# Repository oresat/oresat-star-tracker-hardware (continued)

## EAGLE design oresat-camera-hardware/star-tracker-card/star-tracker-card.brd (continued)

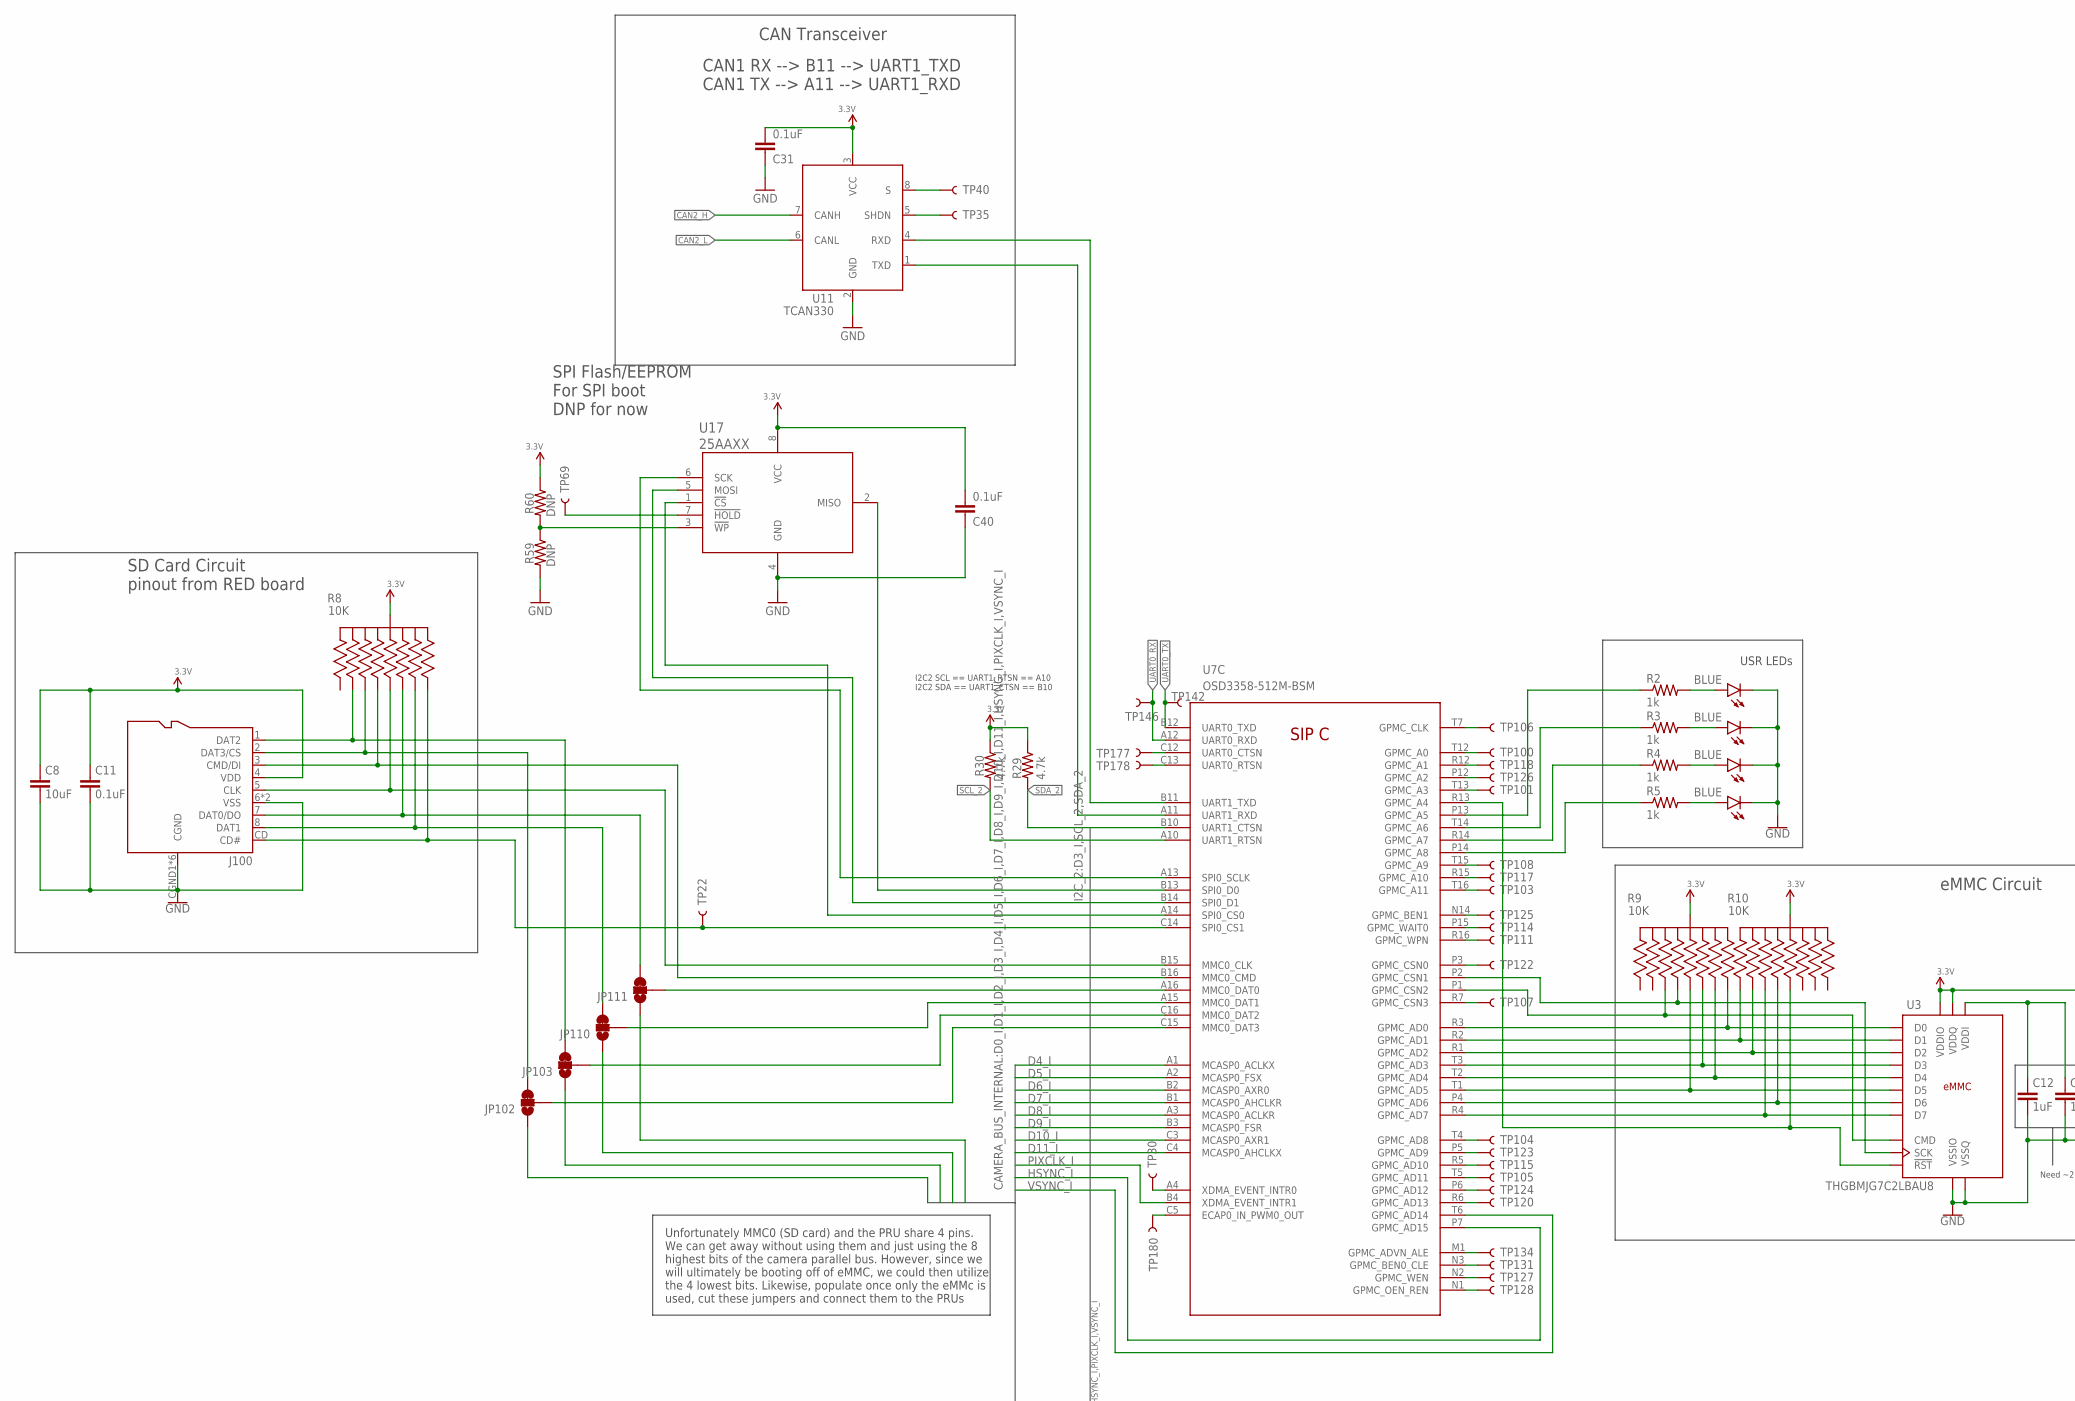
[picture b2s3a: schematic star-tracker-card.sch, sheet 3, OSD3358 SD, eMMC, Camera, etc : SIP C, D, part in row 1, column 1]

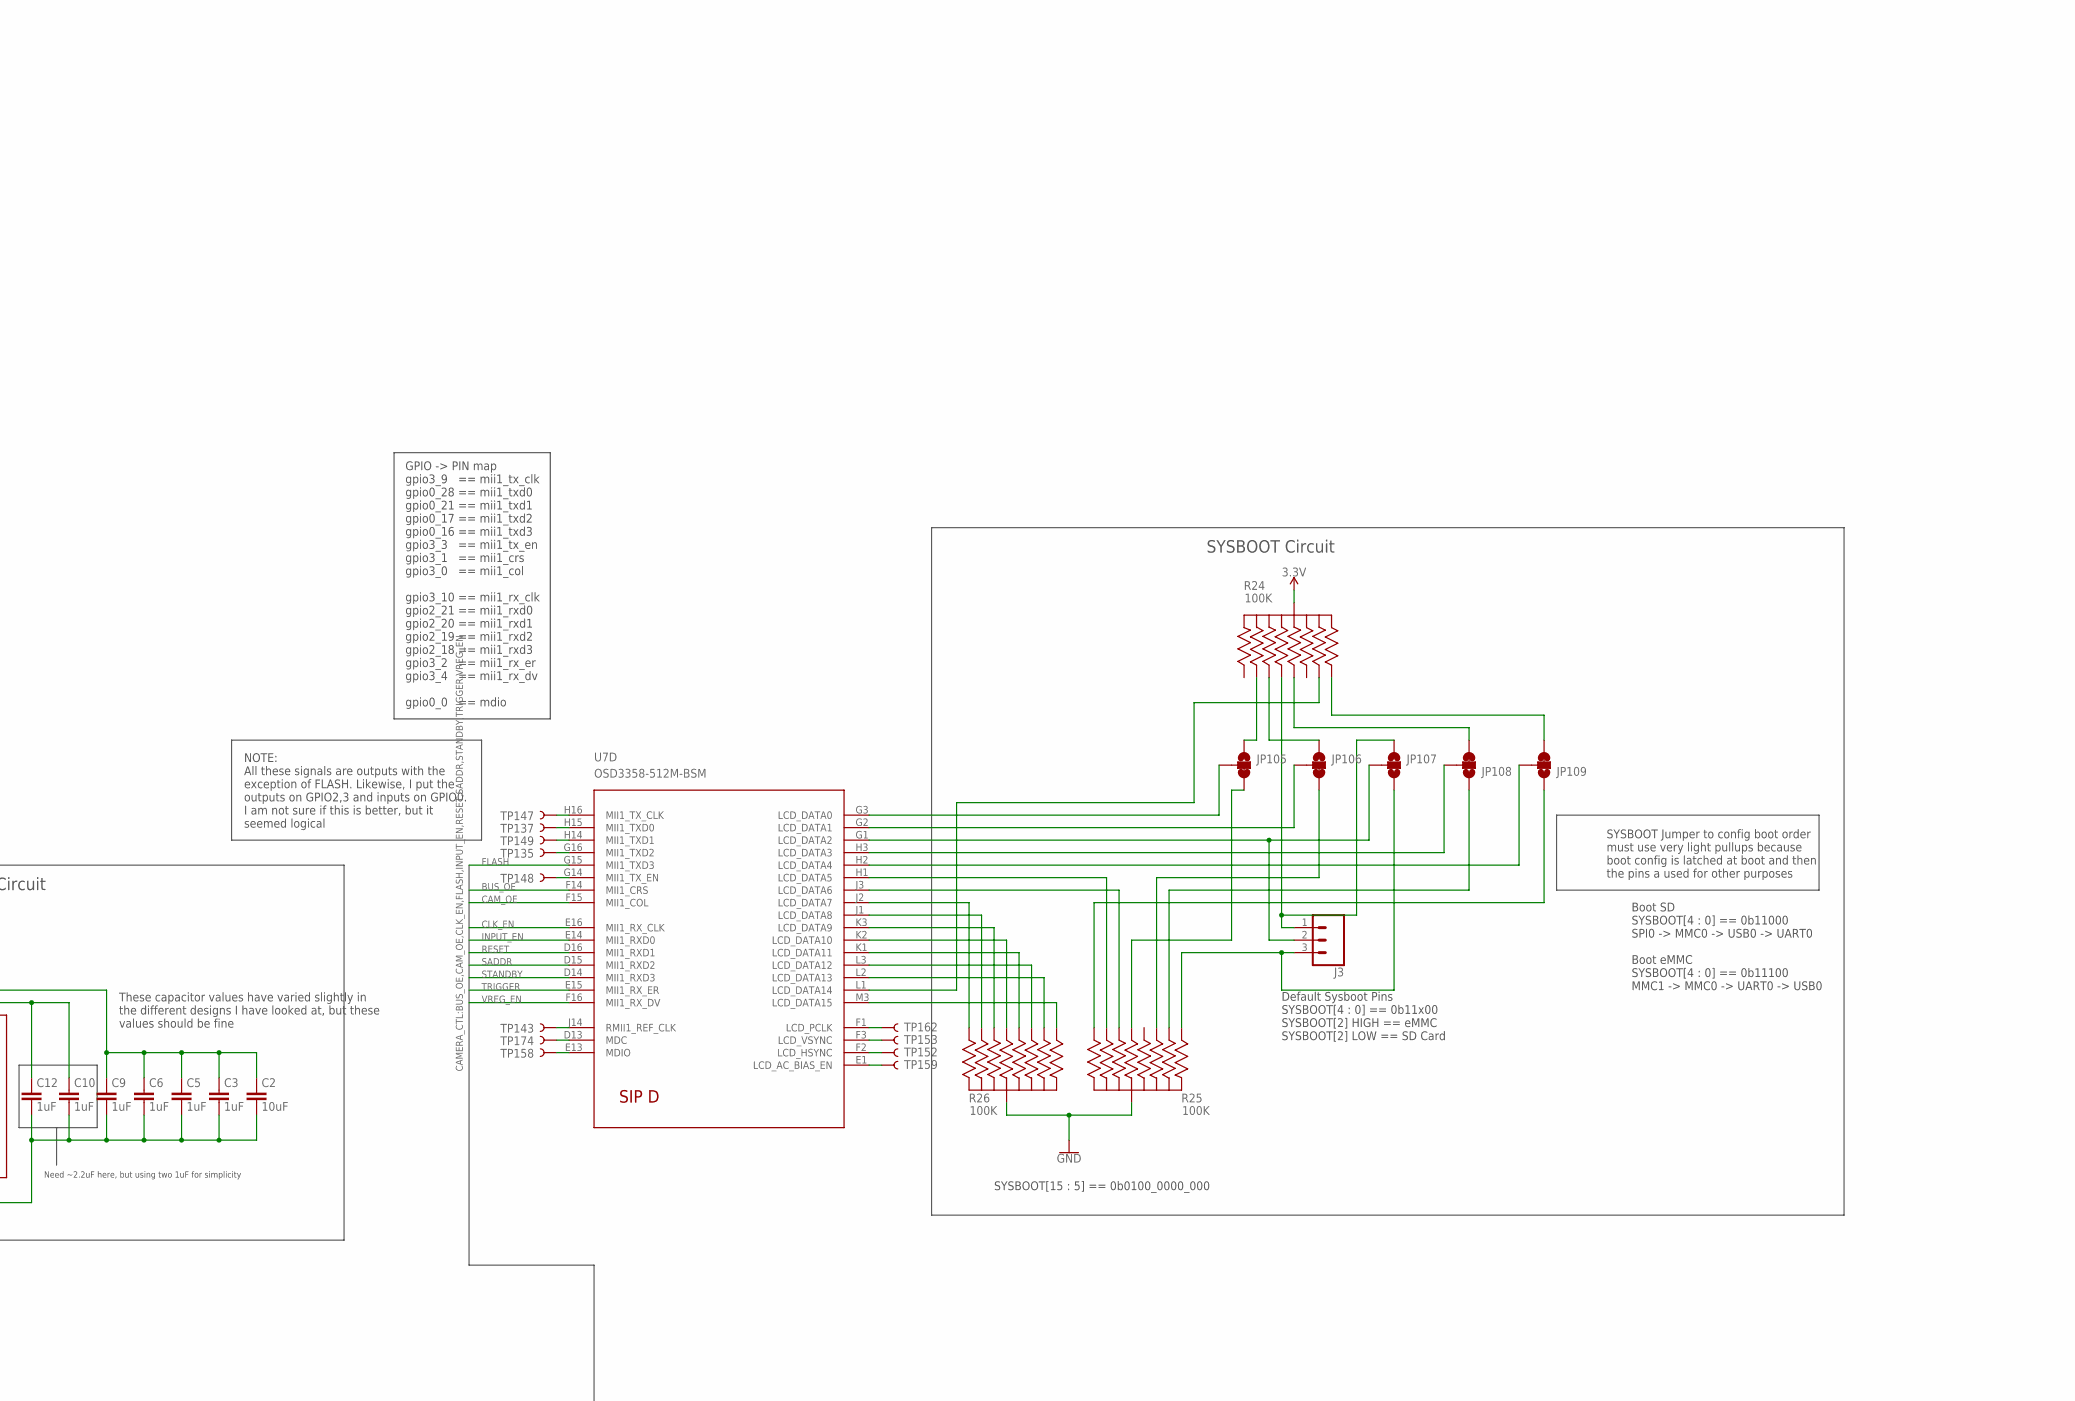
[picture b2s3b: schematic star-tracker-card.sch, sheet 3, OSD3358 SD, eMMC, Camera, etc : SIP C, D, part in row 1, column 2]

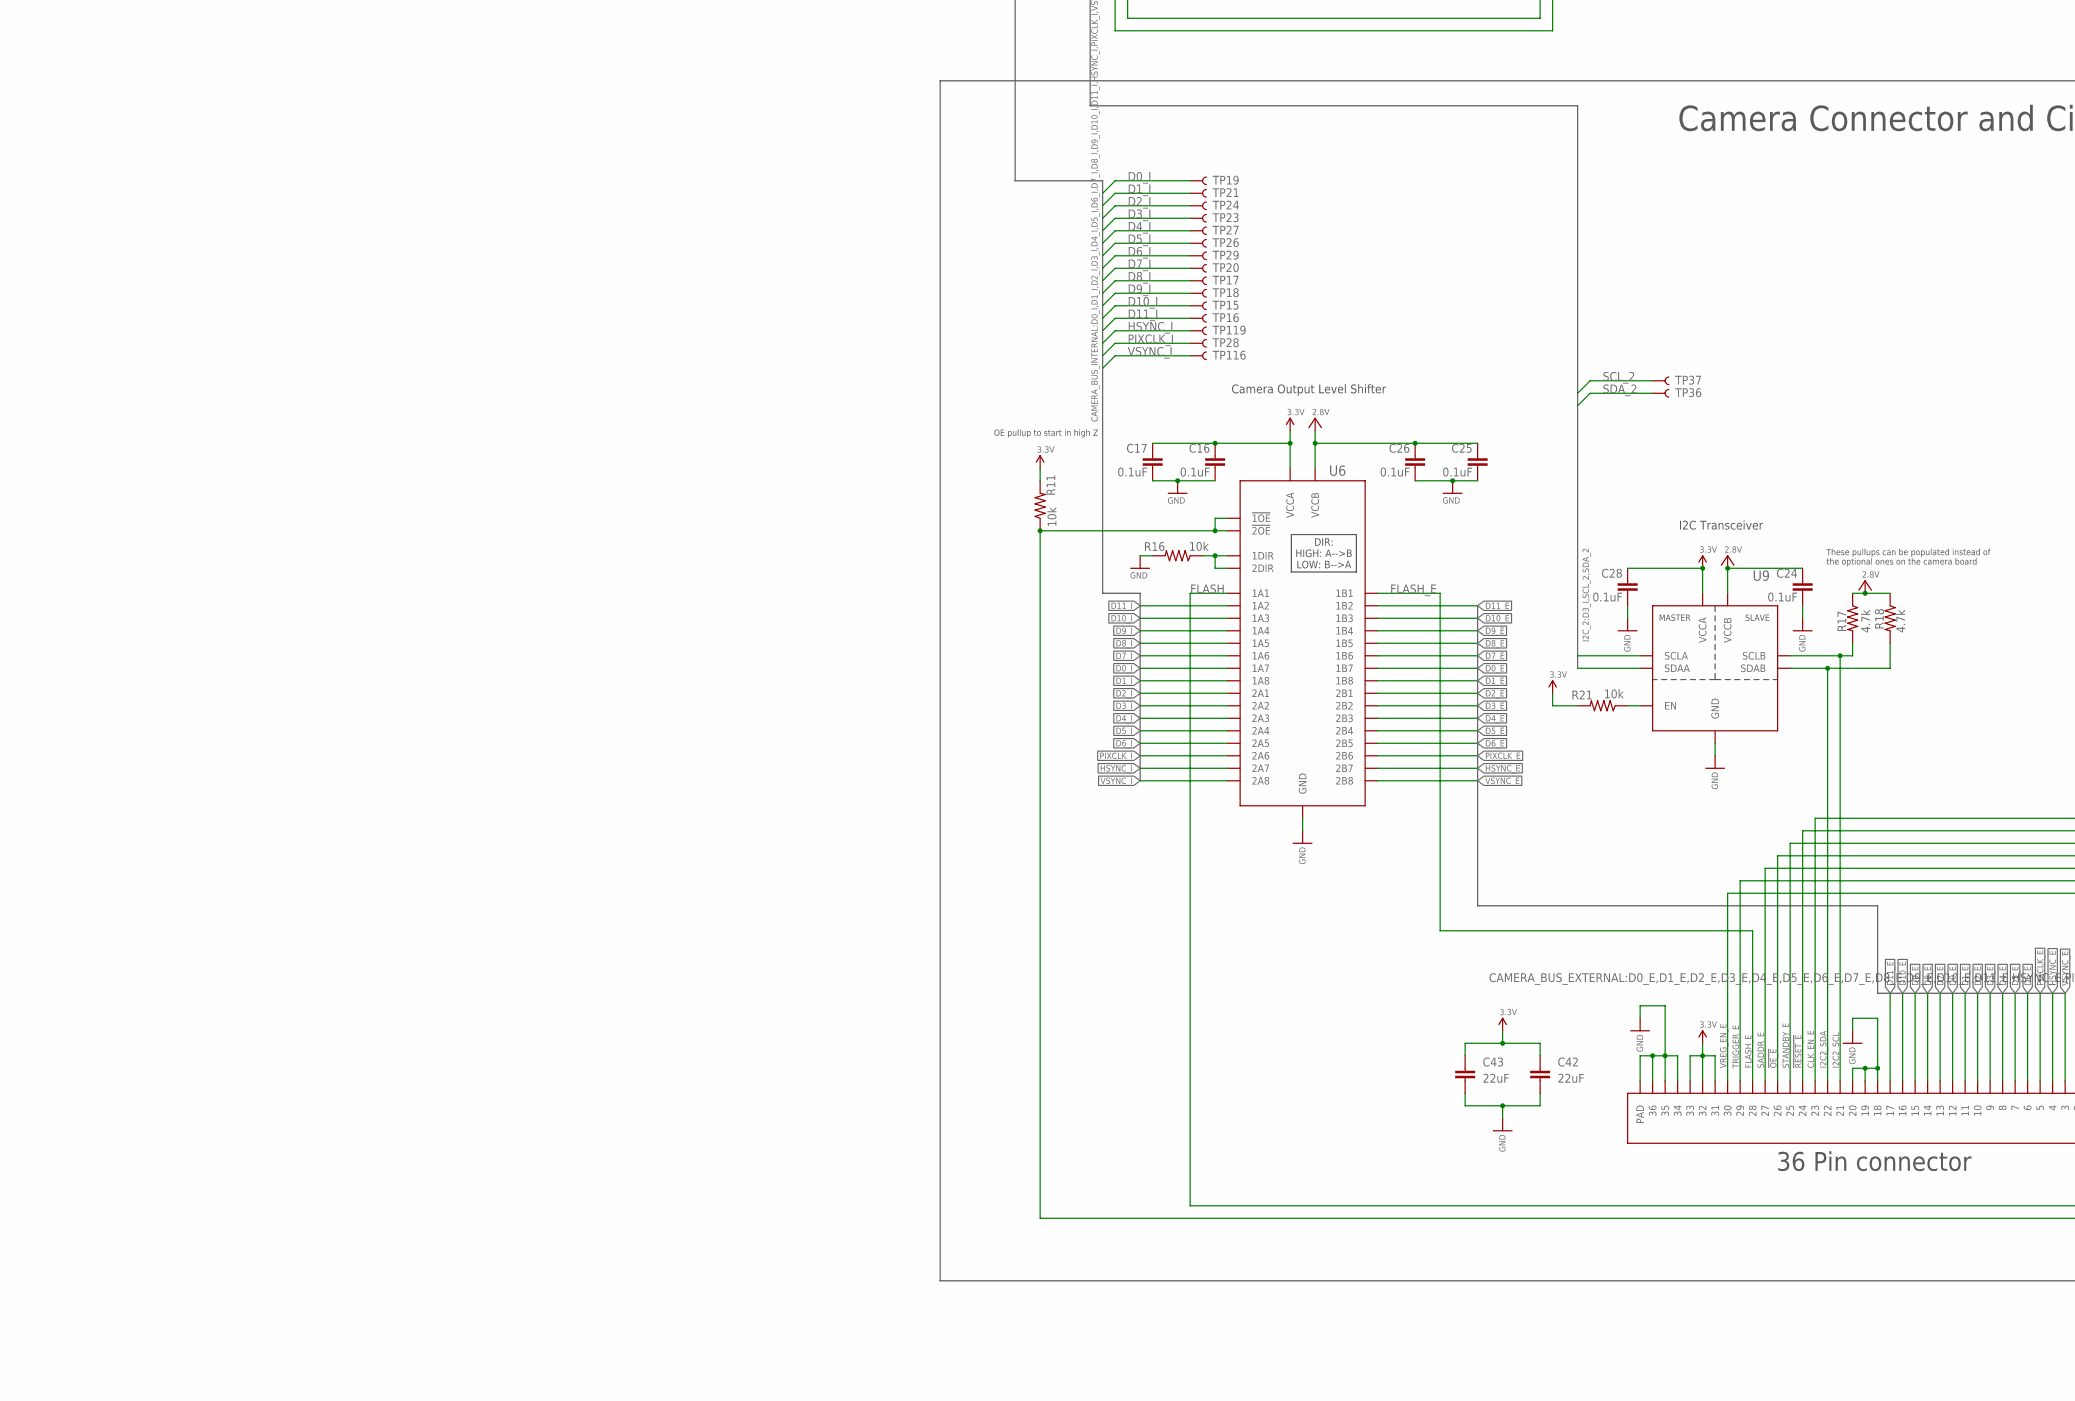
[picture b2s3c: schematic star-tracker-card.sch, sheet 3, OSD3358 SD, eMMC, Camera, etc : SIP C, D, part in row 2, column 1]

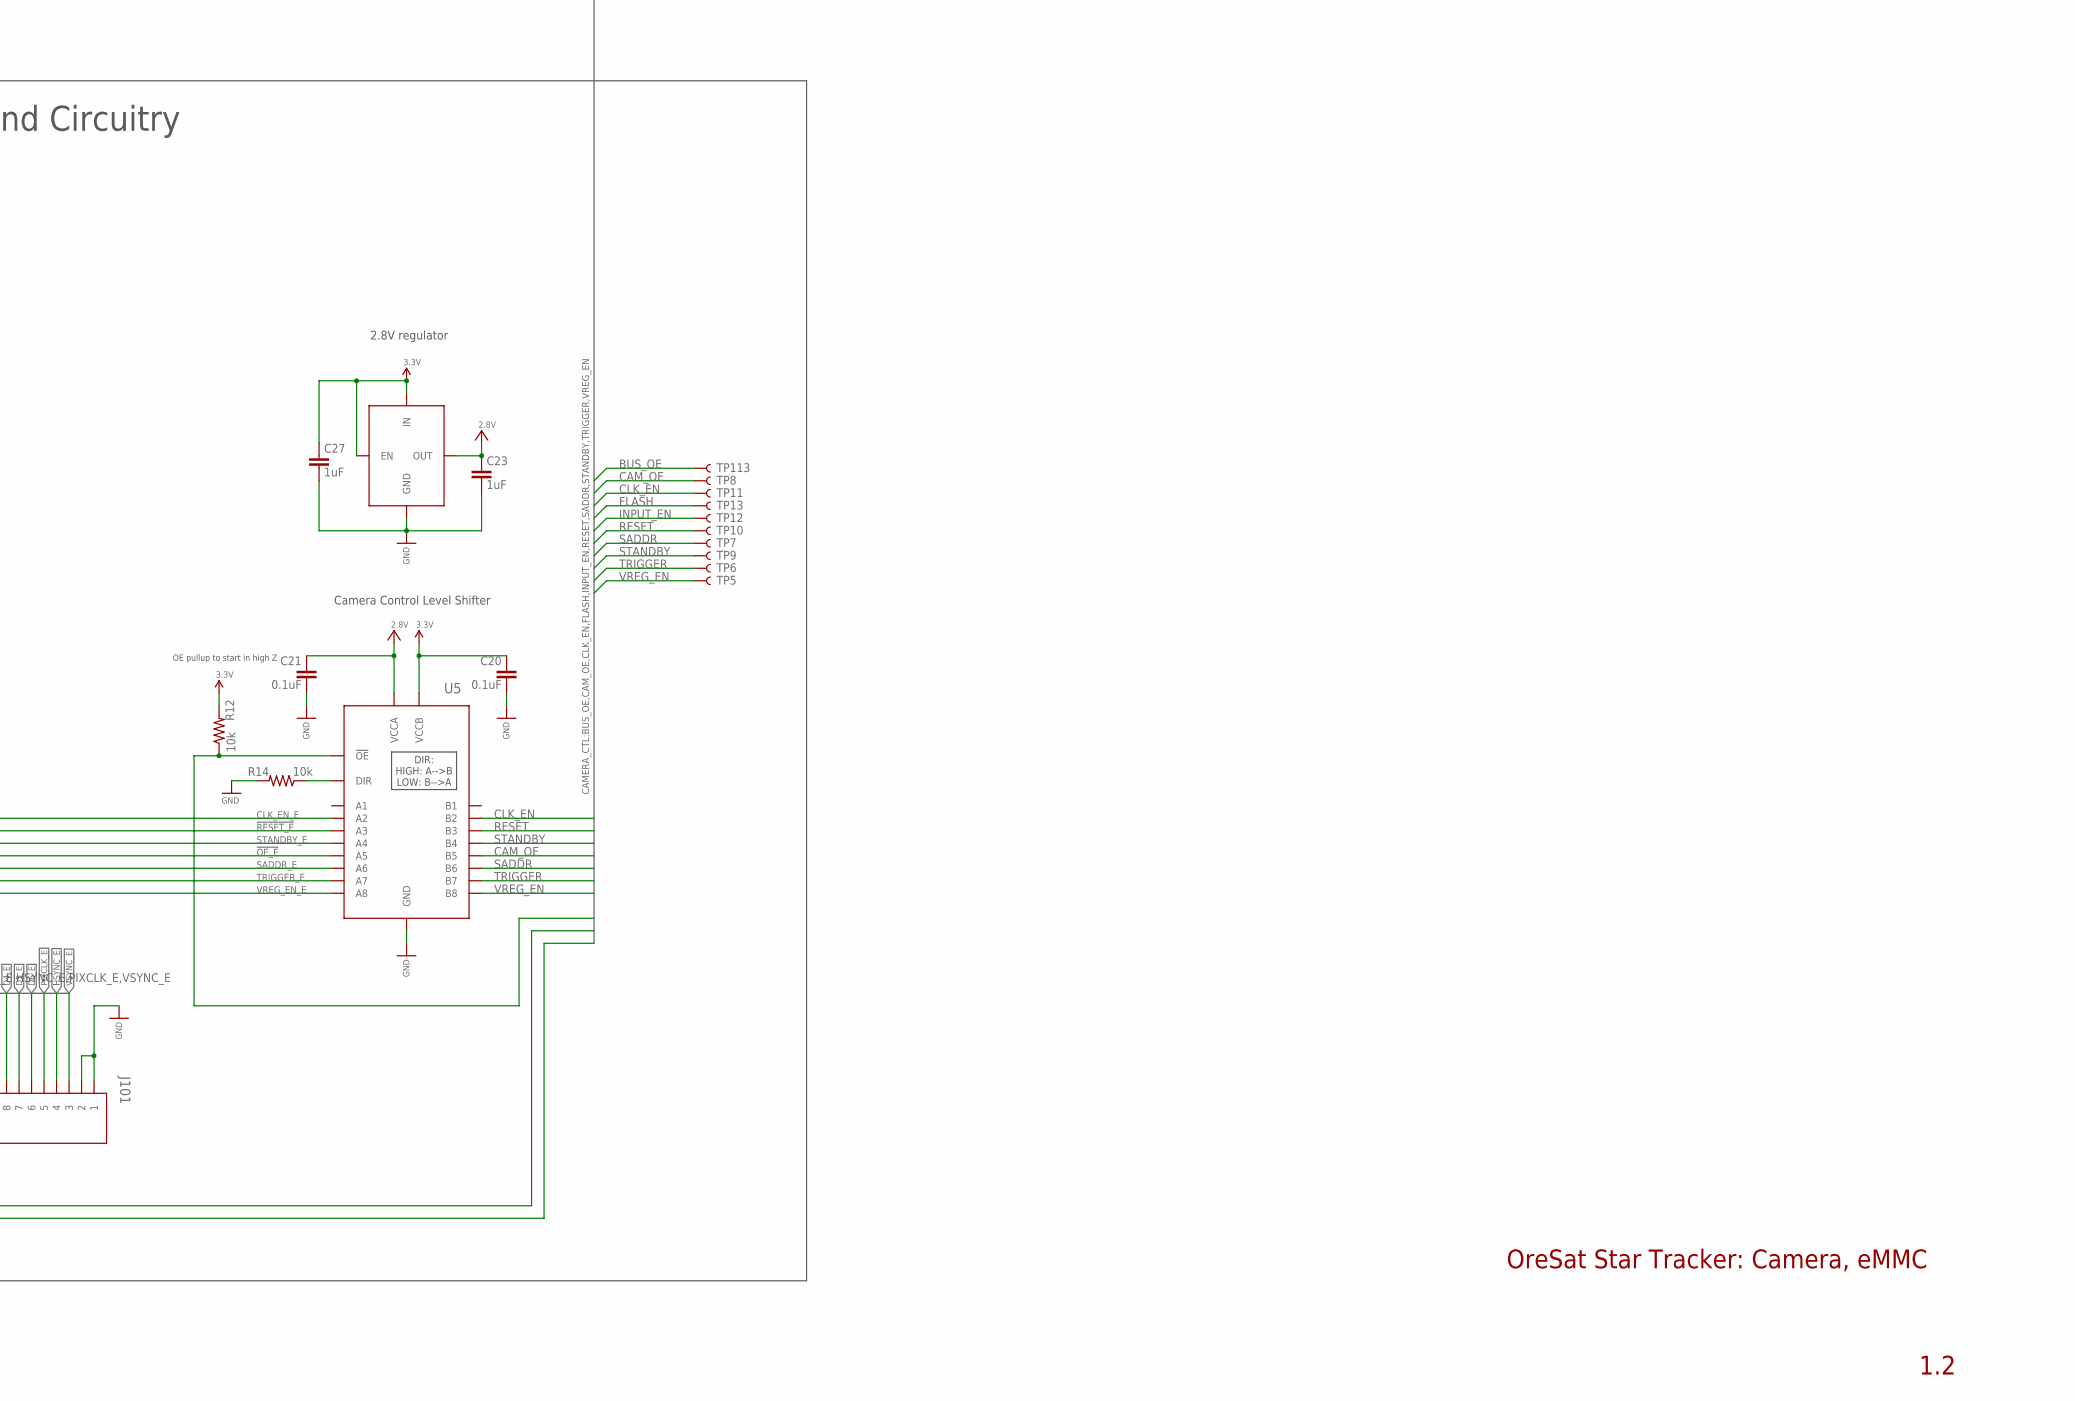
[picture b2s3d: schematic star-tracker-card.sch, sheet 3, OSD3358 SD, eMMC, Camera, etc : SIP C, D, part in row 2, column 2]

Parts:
C2, C8: 10uF; .0805-B
C3, C5, C6, C9, C10, C12, C23, C27: 1uF; .0603-A
C11, C16, C17, C20, C21, C24, C25, C26, C28, C31, C40: 0.1uF; .0603-A
C42, C43: 22uF; C1210
D2, D3, D4, D5: BLUE; LED-0603
J3: CONN_03LONGPADS; 1X03_LONGPADS
J100: DM3BT-DSF-PEJS
J101: 3-1734592-64-1734592-0; TE_3-1734592-6
JP102, JP103, JP105, JP106, JP108, JP109, JP110, JP111: JUMPER-SMT_3_1-NC_TRACE_SILK; SMT-JUMPER_3_1-NC_TRACE_SILK
JP107: JUMPER-SMT_3_NO_SILK; SMT-JUMPER_3_NO_SILK
R2, R3, R4, R5: 1k; .0603-A
R8, R9, R10: 10K; ARRAY_EXBA-M; MPN EXB-A10P103J
R11, R12, R14, R16, R21: 10k; .0603-A
R17, R18, R29, R30: 4.7k; .0603-A
R24, R25, R26: 100K; ARRAY_EXBA-M; MPN EXB-A10P104J
R59, R60: DNP; .0603-A
TP5, TP6, TP7, TP8, TP9, TP10, TP11, TP12, TP13, TP15, TP16, TP17, TP18, TP19, TP20, TP21, TP22, TP23, TP24, TP26, TP27, TP28, TP29, TP30, TP35, TP36, TP37, TP40, TP69, TP100, TP101, TP103, TP104, TP105, TP106, TP107, TP108, TP111, TP113, TP114, TP115, TP116, TP117, TP118, TP119, TP120, TP122, TP123, TP124, TP125, TP126, TP127, TP128, TP131, TP134, TP135, TP137, TP142, TP143, TP146, TP147, TP148, TP149, TP152, TP153, TP158, TP159, TP162, TP174, TP177, TP178, TP180: TEST-POINT3X4; PAD.03X.04
U3: THGBMJG7C2LBAU8; BGA-153(11.5X13)(EMMC-BA); MPN THGBMJG7C2LBAU8
U5: SN74LVC8T245MPWREPPW24-M; PW24-M
U6: CLVCH16T245MDGGREP; DGG48-M
U7: OSD3358-512M-BSM; OSD335X-BGA-256
U8: TLV70028QDDCRQ1; SOT23-5
U9: TCA9509DGKRDGK8-M; DGK8-M
U11: TCAN330; SOT23-8_TI-DCN
U17: 25AAXX; SOIC8

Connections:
2.8V: C21.1, C23.1, C24.1, C25.1, C26.1, R17.1, R18.1, U5.1 (VCCA), U6.7 (VCCB), U6.18 (VCCB), U8.5 (OUT), U9.8 (VCCB)
3.3V: C2.1, C3.1, C5.1, C6.1, C8.1, C9.1, C11.1, C16.1, C17.1, C20.1, C27.1, C28.1, C31.2, C40.2, C42.1, C43.1, J100.4 (VDD), J101.31, J101.32, J101.33, R8.5 (55), R8.10 (55), R9.5 (55), R9.10 (55), R10.5 (55), R10.10 (55), R11.2, R12.2, R21.2, R24.5 (55), R24.10 (55), R29.1, R30.1, R60.1, U3.C6 (VDDQ), U3.E6 (VDDIO), U3.F5 (VDDIO), U3.J10 (VDDIO), U3.K9 (VDDIO), U3.M4 (VDDQ), U3.N4 (VDDQ), U3.P3 (VDDQ), U3.P5 (VDDQ), U5.23 (VCCB), U5.24 (VCCB), U6.31 (VCCA), U6.42 (VCCA), U8.1 (IN), U8.3 (EN), U9.1 (VCCA), U11.3 (VCC), U17.8 (VCC); also elsewhere on the board
!OE_E: J101.26, U5.7 (A5)
!RESET_E: J101.24, U5.5 (A3)
BUS_OE: R11.1, TP113.P$1, U6.25 (!2OE), U6.48 (!1OE), U7.F14 (MII1_CRS)
CAM_OE: TP8.P$1, U5.17 (B5), U7.F15 (MII1_COL)
CAN2_H: U11.7 (CANH); also elsewhere on the board
CAN2_L: U11.6 (CANL); also elsewhere on the board
CLK_EN: TP11.P$1, U5.20 (B2), U7.E16 (MII1_RX_CLK)
CLK_EN_E: J101.23, U5.4 (A2)
D0_E: J101.12, U6.11 (1B7)
D0_I: JP102.1, TP19.P$1, U6.38 (1A7)
D1_E: J101.11, U6.12 (1B8)
D1_I: JP103.1, TP21.P$1, U6.37 (1A8)
D2_E: J101.10, U6.13 (2B1)
D2_I: JP110.1, TP24.P$1, U6.36 (2A1)
D3_E: J101.9, U6.14 (2B2)
D3_I: JP111.1, TP23.P$1, U6.35 (2A2)
D4_E: J101.8, U6.16 (2B3)
D4_I: TP27.P$1, U6.33 (2A3), U7.A1 (MCASP0_ACLKX)
D5_E: J101.7, U6.17 (2B4)
D5_I: TP26.P$1, U6.32 (2A4), U7.A2 (MCASP0_FSX)
D6_E: J101.6, U6.19 (2B5)
D6_I: TP29.P$1, U6.30 (2A5), U7.B2 (MCASP0_AXR0)
D7_E: J101.13, U6.9 (1B6)
D7_I: TP20.P$1, U6.40 (1A6), U7.B1 (MCASP0_AHCLKR)
D8_E: J101.14, U6.8 (1B5)
D8_I: TP17.P$1, U6.41 (1A5), U7.A3 (MCASP0_ACLKR)
D9_E: J101.15, U6.6 (1B4)
D9_I: TP18.P$1, U6.43 (1A4), U7.B3 (MCASP0_FSR)
D10_E: J101.16, U6.5 (1B3)
D10_I: TP15.P$1, U6.44 (1A3), U7.C3 (MCASP0_AXR1)
D11_E: J101.17, U6.3 (1B2)
D11_I: TP16.P$1, U6.46 (1A2), U7.C4 (MCASP0_AHCLKX)
FLASH: TP13.P$1, U6.47 (1A1), U7.G15 (MII1_TXD3)
FLASH_E: J101.28, U6.2 (1B1)
GND: C2.2, C3.2, C5.2, C6.2, C8.2, C9.2, C10.2, C11.2, C12.2, C16.2, C17.2, C20.2, C21.2, C23.2, C24.2, C25.2, C26.2, C27.2, C28.2, C31.1, C40.1, C42.2, C43.2, D2.C, D3.C, D4.C, D5.C, J100.6 (VSS), J100.CGND1 (CGND), J100.CGND2 (CGND), J100.CGND3 (CGND), J100.CGND4 (CGND), J100.CGND5 (CGND), J100.CGND6 (CGND), J100.GND (VSS), J101.1, J101.2, J101.18, J101.19, J101.20, J101.34, J101.35, J101.36, J101.S1 (PAD), J101.S2 (PAD), R14.2, R16.2, R25.5 (55), R25.10 (55), R26.5 (55), R26.10 (55), R59.2, U3.C4 (VSSQ), U3.E7 (VSSIO), U3.G5 (VSSIO), U3.H10 (VSSIO), U3.J5 (VSSIO), U3.K8 (VSSIO), U3.N2 (VSSQ), U3.N5 (VSSQ), U3.P4 (VSSQ), U3.P6 (VSSQ), U5.11 (GND), U5.12 (GND), U5.13 (GND), U6.4 (GND), U6.10 (GND), U6.15 (GND), U6.21 (GND), U6.28 (GND), U6.34 (GND), U6.39 (GND), U6.45 (GND), U8.2 (GND), U9.4 (GND), U11.2 (GND), U17.4 (GND); also elsewhere on the board
HSYNC_E: J101.4, U6.22 (2B7)
HSYNC_I: TP119.P$1, U6.27 (2A7), U7.P7 (GPMC_AD15)
I2C2_SCL: J101.21, R17.2, U9.7 (SCLB)
I2C2_SDA: J101.22, R18.2, U9.6 (SDAB)
INPUT_EN: R12.1, TP12.P$1, U5.22 (!OE), U7.E14 (MII1_RXD0)
unnamed: D5.A, R5.2
unnamed: J100.1 (DAT2), JP103.3, R8.9 (99)
unnamed: J100.2 (DAT3/CS), JP102.3, R8.2 (22)
unnamed: J100.3 (CMD/DI), R8.8 (88), U7.B16 (MMC0_CMD)
unnamed: J100.5 (CLK), R8.3 (33), U7.B15 (MMC0_CLK)
unnamed: J100.7 (DAT0/DO), JP111.3, R8.7 (77)
unnamed: J100.8 (DAT1), JP110.3, R8.4 (44)
unnamed: J100.CD (CD#), R8.6 (66), TP22.P$1, U7.C14 (SPI0_CS1)
unnamed: U7.B11 (UART1_TXD), U11.4 (RXD)
unnamed: U7.A11 (UART1_RXD), U11.1 (TXD)
unnamed: TP40.P$1, U11.8 (S)
unnamed: TP35.P$1, U11.5 (SHDN)
unnamed: JP111.2, U7.A16 (MMC0_DAT0)
unnamed: JP110.2, U7.A15 (MMC0_DAT1)
unnamed: JP103.2, U7.C16 (MMC0_DAT2)
unnamed: JP102.2, U7.C15 (MMC0_DAT3)
unnamed: R16.1, U6.1 (1DIR), U6.24 (2DIR)
unnamed: R21.1, U9.5 (EN)
unnamed: R14.1, U5.2 (DIR)
unnamed: U7.A13 (SPI0_SCLK), U17.6 (SCK)
unnamed: U7.B13 (SPI0_D0), U17.2 (MISO)
unnamed: U7.B14 (SPI0_D1), U17.5 (MOSI)
unnamed: U7.A14 (SPI0_CS0), U17.1 (!CS)
unnamed: TP30.P$1, U7.A4 (XDMA_EVENT_INTR0)
unnamed: TP180.P$1, U7.C5 (ECAP0_IN_PWM0_OUT)
unnamed: TP104.P$1, U7.T4 (GPMC_AD8)
unnamed: TP123.P$1, U7.P5 (GPMC_AD9)
unnamed: TP115.P$1, U7.R5 (GPMC_AD10)
unnamed: TP105.P$1, U7.T5 (GPMC_AD11)
unnamed: TP124.P$1, U7.P6 (GPMC_AD12)
unnamed: TP120.P$1, U7.R6 (GPMC_AD13)
unnamed: TP125.P$1, U7.N14 (GPMC_BEN1)
unnamed: TP114.P$1, U7.P15 (GPMC_WAIT0)
unnamed: TP111.P$1, U7.R16 (GPMC_WPN)
unnamed: TP177.P$1, U7.C12 (UART0_CTSN)
unnamed: TP178.P$1, U7.C13 (UART0_RTSN)
unnamed: TP162.P$1, U7.F1 (LCD_PCLK)
unnamed: TP153.P$1, U7.F3 (LCD_VSYNC)
unnamed: TP152.P$1, U7.F2 (LCD_HSYNC)
unnamed: TP159.P$1, U7.E1 (LCD_AC_BIAS_EN)
unnamed: TP143.P$1, U7.J14 (RMII1_REF_CLK)
unnamed: TP174.P$1, U7.D13 (MDC)
unnamed: TP158.P$1, U7.E13 (MDIO)
unnamed: TP147.P$1, U7.H16 (MII1_TX_CLK)
unnamed: TP137.P$1, U7.H15 (MII1_TXD0)
unnamed: TP149.P$1, U7.H14 (MII1_TXD1)
unnamed: TP135.P$1, U7.G16 (MII1_TXD2)
unnamed: TP106.P$1, U7.T7 (GPMC_CLK)
unnamed: TP100.P$1, U7.T12 (GPMC_A0)
unnamed: TP118.P$1, U7.R12 (GPMC_A1)
unnamed: TP126.P$1, U7.P12 (GPMC_A2)
unnamed: TP101.P$1, U7.T13 (GPMC_A3)
unnamed: D4.A, R4.2
unnamed: D3.A, R3.2
unnamed: TP108.P$1, U7.T15 (GPMC_A9)
unnamed: TP117.P$1, U7.R15 (GPMC_A10)
unnamed: TP103.P$1, U7.T16 (GPMC_A11)
unnamed: TP122.P$1, U7.P3 (GPMC_CSN0)
unnamed: TP107.P$1, U7.R7 (GPMC_CSN3)
unnamed: D2.A, R2.2
unnamed: TP134.P$1, U7.M1 (GPMC_ADVN_ALE)
unnamed: TP131.P$1, U7.N3 (GPMC_BEN0_CLE)
unnamed: TP127.P$1, U7.N2 (GPMC_WEN)
unnamed: TP128.P$1, U7.N1 (GPMC_OEN_REN)
unnamed: TP148.P$1, U7.G14 (MII1_TX_EN)
unnamed: JP105.1, R24.9 (99)
unnamed: JP106.1, R24.2 (22)
unnamed: JP108.3, R24.3 (33)
unnamed: JP109.3, R24.6 (66)
unnamed: J3.1, JP107.1, R24.8 (88)
unnamed: R59.1, R60.2, U17.3 (!WP)
unnamed: TP69.P$1, U17.7 (!HOLD)
unnamed: JP105.2, U7.G3 (LCD_DATA0)
unnamed: JP106.2, U7.G2 (LCD_DATA1)
unnamed: J3.2, JP107.2, U7.G1 (LCD_DATA2)
unnamed: JP108.2, U7.H3 (LCD_DATA3)
unnamed: JP109.2, U7.H2 (LCD_DATA4)
unnamed: R25.4 (44), U7.H1 (LCD_DATA5)
unnamed: R25.7 (77), U7.J3 (LCD_DATA6)
unnamed: R26.4 (44), U7.J1 (LCD_DATA8)
unnamed: R26.7 (77), U7.K3 (LCD_DATA9)
unnamed: R26.3 (33), U7.K2 (LCD_DATA10)
unnamed: R26.8 (88), U7.K1 (LCD_DATA11)
unnamed: R26.2 (22), U7.L3 (LCD_DATA12)
unnamed: R26.9 (99), U7.L2 (LCD_DATA13)
unnamed: R24.4 (44), U7.L1 (LCD_DATA14)
unnamed: R26.1 (11), U7.M3 (LCD_DATA15)
unnamed: R26.6 (66), U7.J2 (LCD_DATA7)
unnamed: JP109.1, R25.6 (66)
unnamed: J3.3, JP107.3, R25.1 (11)
unnamed: JP108.1, R25.9 (99)
unnamed: JP106.3, R25.2 (22)
unnamed: JP105.3, R25.3 (33)
unnamed: C10.1, C12.1, U3.C2 (VDDI)
unnamed: R9.6 (66), U3.A3 (D0), U7.R3 (GPMC_AD0)
unnamed: R10.1 (11), U3.A4 (D1), U7.R2 (GPMC_AD1)
unnamed: R10.9 (99), U3.A5 (D2), U7.R1 (GPMC_AD2)
unnamed: R9.7 (77), U3.B2 (D3), U7.T3 (GPMC_AD3)
unnamed: R9.4 (44), U3.B3 (D4), U7.T2 (GPMC_AD4)
unnamed: R9.3 (33), U3.B4 (D5), U7.T1 (GPMC_AD5)
unnamed: R10.8 (88), U3.B5 (D6), U7.P4 (GPMC_AD6)
unnamed: R10.2 (22), U3.B6 (D7), U7.R4 (GPMC_AD7)
unnamed: R9.2 (22), U3.M5 (CMD), U7.P1 (GPMC_CSN2)
unnamed: R9.8 (88), U3.M6 (SCK), U7.P2 (GPMC_CSN1)
unnamed: R10.3 (33), U3.K5 (!RST!), U7.R13 (GPMC_A4)
unnamed: R2.1, U7.P13 (GPMC_A5)
unnamed: R3.1, U7.T14 (GPMC_A6)
unnamed: R4.1, U7.R14 (GPMC_A7)
unnamed: R5.1, U7.P14 (GPMC_A8)
PIXCLK_E: J101.5, U6.20 (2B6)
PIXCLK_I: TP28.P$1, U6.29 (2A6), U7.B4 (XDMA_EVENT_INTR1)
RESET: TP10.P$1, U5.19 (B3), U7.D16 (MII1_RXD1)
SADDR: TP7.P$1, U5.16 (B6), U7.D15 (MII1_RXD2)
SADDR_E: J101.27, U5.8 (A6)
SCL_2: R30.2, TP37.P$1, U7.A10 (UART1_RTSN), U9.2 (SCLA)
SDA_2: R29.2, TP36.P$1, U7.B10 (UART1_CTSN), U9.3 (SDAA)
STANDBY: TP9.P$1, U5.18 (B4), U7.D14 (MII1_RXD3)
STANDBY_E: J101.25, U5.6 (A4)
TRIGGER: TP6.P$1, U5.15 (B7), U7.E15 (MII1_RX_ER)
TRIGGER_E: J101.29, U5.9 (A7)
UART0_RX: TP146.P$1, U7.A12 (UART0_RXD); also elsewhere on the board
UART0_TX: TP142.P$1, U7.B12 (UART0_TXD); also elsewhere on the board
VREG_EN: TP5.P$1, U5.14 (B8), U7.F16 (MII1_RX_DV)
VREG_EN_E: J101.30, U5.10 (A8)
VSYNC_E: J101.3, U6.23 (2B8)
VSYNC_I: TP116.P$1, U6.26 (2A8), U7.T6 (GPMC_AD14)

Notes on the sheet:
SYSBOOT Jumper to config boot order must use very light pullups because boot config is latched at boot and then the pins a used for other purposes
SYSBOOT[15 : 5] == 0b0100_0000_000
Boot SD SYSBOOT[4 : 0] == 0b11000 SPI0 -> MMC0 -> USB0 -> UART0 Boot eMMC SYSBOOT[4 : 0] == 0b11100 MMC1 -> MMC0 -> UART0 -> USB0
USR LEDs
These capacitor values have varied slightly in the different designs I have looked at, but these values should be fine
eMMC Circuit
SD Card Circuit pinout from RED board
SYSBOOT Circuit
CAN Transceiver
CAN1 RX --> B11 --> UART1_TXD CAN1 TX --> A11 --> UART1_RXD
36 Pin connector
Unfortunately MMC0 (SD card) and the PRU share 4 pins. We can get away without using them and just using the 8 highest bits of the camera parallel bus. However, since we will ultimately be booting off of eMMC, we could then utilize the 4 lowest bits. Likewise, populate once only the eMMc is used, c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
I2C2 SCL == UART1_RTSN == A10 I2C2 SDA == UART1_CTSN == B10
GPIO -> PIN map gpio3_9 == mii1_tx_clk gpio0_28 == mii1_txd0 gpio0_21 == mii1_txd1 gpio0_17 == mii1_txd2 gpio0_16 == mii1_txd3 gpio3_3 == mii1_tx_en gpio3_1 == mii1_crs gpio3_0 == mii1_col gpio3_10 == mii1_rx_clk gpio2_21 == mii1_rxd0 gpio2_20 == mii1_rxd1 gpio2_19 == mii1_rxd2 gpio2_18 == mii1_rxd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
OE pullup to start in high Z
These pullups can be populated instead of the optional ones on the camera board
Camera Output Level Shifter
Camera Control Level Shifter
2.8V regulator
I2C Transceiver
NOTE: All these signals are outputs with the exception of FLASH. Likewise, I put the outputs on GPIO2,3 and inputs on GPIO0. I am not sure if this is better, but it seemed logical
Camera Connector and Circuitry
Need ~2.2uF here, but using two 1uF for simplicity
Default Sysboot Pins SYSBOOT[4 : 0] == 0b11x00 SYSBOOT[2] HIGH == eMMC SYSBOOT[2] LOW == SD Card
SPI Flash/EEPROM For SPI boot DNP for now
OreSat Star Tracker: Camera, eMMC
1.2
